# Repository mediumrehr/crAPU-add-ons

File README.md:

# crAPU-add-ons
a crappy Audio Processing Unit SAO for DEF CON 26 badges; specifically, the zinthesizer was designed for the [DCZia DC26 badge](https://github.com/dczia/Defcon26-Badge) and the scaremin was designed for [Chris Gammell's](https://twitter.com/Chris_Gammell) Goodfear badge.

[video demo](https://www.youtube.com/watch?v=xHMZxM6m_c0)

crAPUs were designed to add audio sythesis/playback capabilities to badges that didn't have any. Since i2c would not be fast enough to drive an external digital to analog converter (DAC), the crAPUs feature their own processor (SAM21G18) to generate tones, and the note and volume can be selected over i2c.

## Installing/Updating Firmware

### Setup

Firmware can be loaded with [Atmel Studio 7.0](https://www.microchip.com/mplab/avr-support/atmel-studio-7), or install the packages below to use with your preferred text editor and compile with arm gcc.

#### arm gcc and gdb

MacOS

```
brew install armmbed/formulae/arm-none-eabi-gcc
```

#### jlink gdb server

Download install file from [segger.com](https://www.segger.com/products/debug-probes/j-link/tools/j-link-gdb-server/about-j-link-gdb-server/)

#### SWD connection

Software debug (SWD) pins are labelled on the back-right of the boards. Connect SWDIO, SWCLK, 3V3, RESET, and GND as labelled. SWD requires the board to be powered external from the SWD port, so it's easiest to power the board from the 3V3 and GND pins on the SAO header.

### Build

```
cd firmware/crAPU/
make -C Build/
```

### Load

#### jlink

Start jlink gdb server in one tab

```
JLinkGDBServer -if SWD -device ATSAMD21G18
```

Start gdb in another tba

```
arm-none-eabi-gdb Build/crAPU.elf
(gdb) target extended-remote :2331
```

Load new firmware, reset microcontroller, and run new code

```
(gdb) load
(gdb) monitor reset
(gdb) c
```

## Usage

The crAPU can be controlled via i2c at address `0x1A`. The add-on will listen for two bytes, the first byte will set the note (0 - 127 using MIDI table), and the second byte will set the volume (0 - 127). If `128 (0x80)` is sent as the MIDI note, it will be interpreted as a note off command.

#### DCZia Badge

Load my [DCZia fork](https://github.com/mediumrehr/Defcon26-Badge) onto the DCZia badge. Attach the zinthesizer add-on, turn on the badge, and within menu mode, select button 7 (left column, third down). The display should now say it's in zinthesizer mode and each key will play a unique note.

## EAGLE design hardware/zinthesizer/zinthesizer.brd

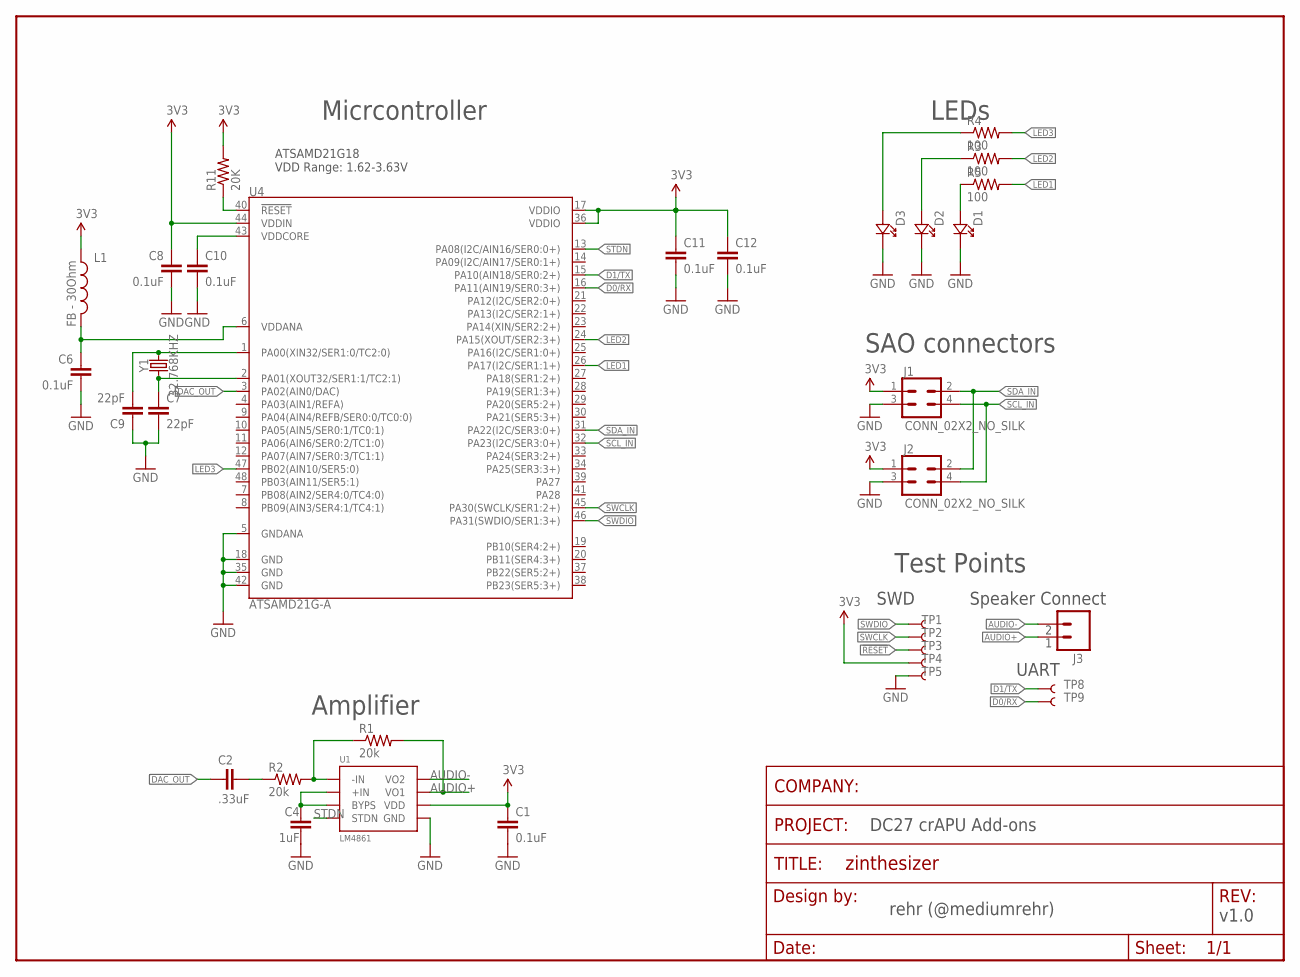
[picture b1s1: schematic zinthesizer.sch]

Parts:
C1, C6, C8, C10, C11, C12: 0.1uF; 0603-CAP
C2: .33uF; 0603-CAP
C4: 1uF; 0603-CAP
C7, C9: 22pF; 0603-CAP
D1, D2, D3: LED1206REVERSE_NO_SILK; 1206_NO_SILK
FRAME1: FRAME-LETTER-BLANKNO_PACKAGE; DUMMY
J1, J2: CONN_02X2_NO_SILK; 2X2_NO_SILK
J3: M02ROUND; M02_ROUND
L1: FB - 30Ohm; 0603
R1, R2: 20k; 0805
R3, R4, R5: 100; 0603-RES
R11: 20K; 0603-RES
TP1, TP2, TP3, TP4, TP5: TEST-POINT3X5; PAD.03X.05
TP8, TP9: TEST-POINT3X4; PAD.03X.04
U1: LM4861; 8-SOIC
U4: ATSAMD21G-A; TQFP-48
Y1: 32.768KHZ; ABS06

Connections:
3.3V: C1.1, C8.1, C11.1, C12.1, J1.1, J2.1, L1.1, R11.2, TP4.P$1, U1.P$6 (VDD), U4.17 (VDDIO), U4.36 (VDDIO), U4.44 (VDDIN)
!RESET: R11.1, TP3.P$1, U4.40 (!RESET!)
AUDIO+: J3.P$1, R1.2, U1.P$5 (VO1)
AUDIO-: J3.P$2, U1.P$8 (VO2)
D0/RX: TP9.P$1, U4.16 (PA11(AIN19/SER0:3+))
D1/TX: TP8.P$1, U4.15 (PA10(AIN18/SER0:2+))
DAC_OUT: C2.2, U4.3 (PA02(AIN0/DAC))
GND: C1.2, C4.2, C6.2, C7.2, C8.2, C9.1, C10.2, C11.2, C12.2, D1.P$1, D2.P$1, D3.P$1, J1.3, J2.3, TP5.P$1, U1.P$7 (GND), U4.5 (GNDANA), U4.18 (GND), U4.35 (GND), U4.42 (GND)
LED1: R5.2, U4.26 (PA17(I2C/SER1:1+))
LED2: R3.2, U4.24 (PA15(XOUT/SER2:3+))
LED3: R4.2, U4.47 (PB02(AIN10/SER5:0))
unnamed: C2.1, R2.1
unnamed: R1.1, R2.2, U1.P$4 (-IN)
unnamed: D1.P$2, R5.1
unnamed: C7.1, U4.2 (PA01(XOUT32/SER1:1/TC2:1)), Y1.P$1 (1)
unnamed: C4.1, U1.P$2 (BYPS), U1.P$3 (+IN)
unnamed: D2.P$2, R3.1
unnamed: D3.P$2, R4.1
unnamed: C9.2, U4.1 (PA00(XIN32/SER1:0/TC2:0)), Y1.P$2 (2)
SCL_IN: J1.4, J2.4, U4.32 (PA23(I2C/SER3:0+))
SDA_IN: J1.2, J2.2, U4.31 (PA22(I2C/SER3:0+))
STDN: U1.P$1 (STDN), U4.13 (PA08(I2C/AIN16/SER0:0+))
SWCLK: TP2.P$1, U4.45 (PA30(SWCLK/SER1:2+))
SWDIO: TP1.P$1, U4.46 (PA31(SWDIO/SER1:3+))
VDDANA: C6.1, L1.2, U4.6 (VDDANA)
VDDCORE: C10.1, U4.43 (VDDCORE)

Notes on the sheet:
ATSAMD21G18 VDD Range: 1.62-3.63V
DC27 crAPU Add-ons
rehr (@mediumrehr)
v1.0
Micrcontroller
LEDs
SAO connectors
Test Points
Amplifier
SWD
Speaker Connect
UART

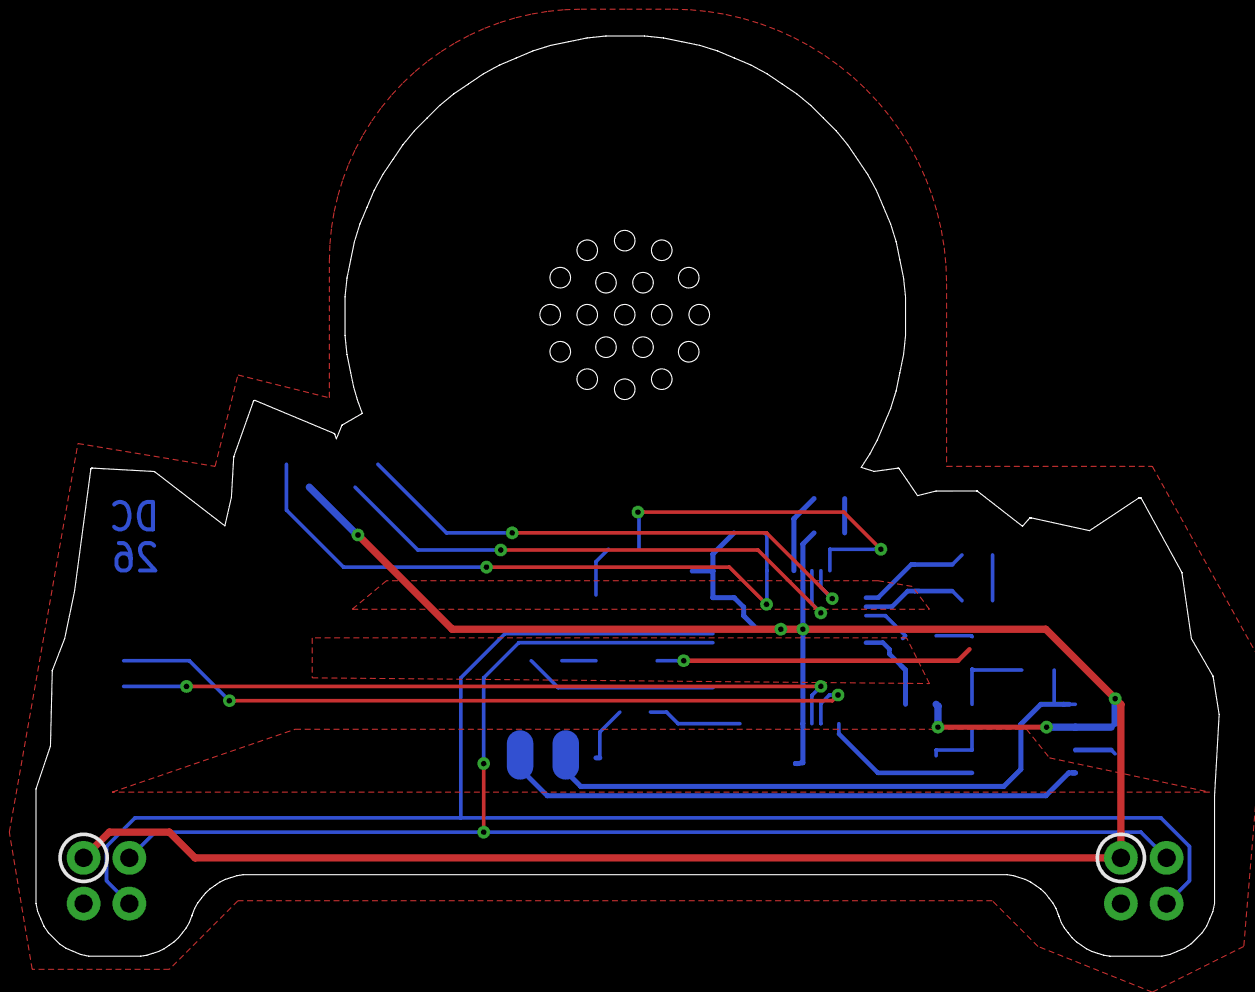
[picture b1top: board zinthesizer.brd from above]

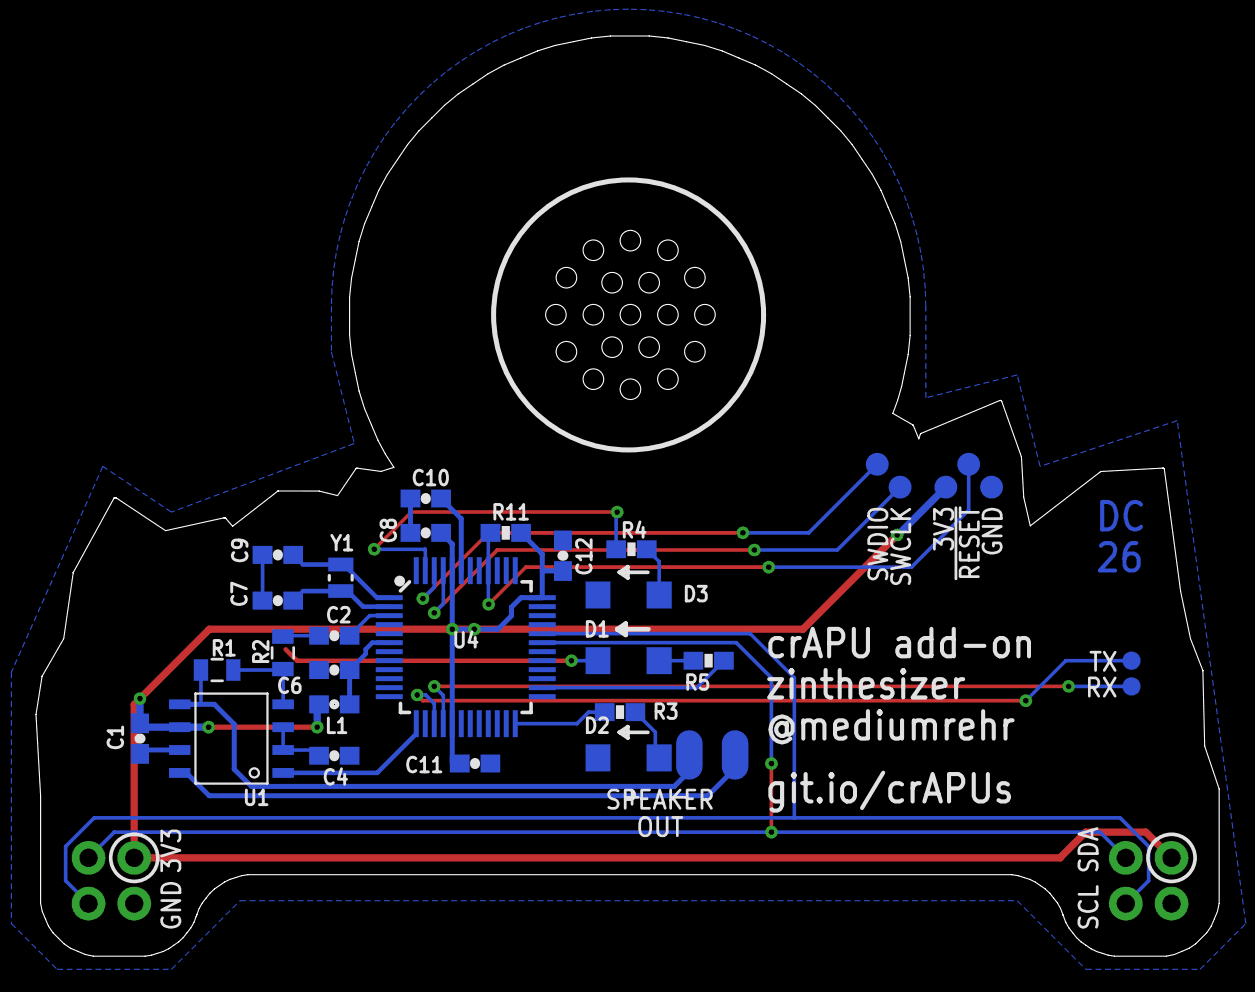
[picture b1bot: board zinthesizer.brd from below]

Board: 2 copper layers, 65.7 x 51.1 mm, 34 parts (31 on the bottom side), 26 nets.

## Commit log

2019-04-19 fix readme typo
2019-04-26 enable DAC (only 440Hz output)
2019-04-27 add i2c AND basic pitch control over i2c
2019-04-28 add hardware design files and BOM
2019-04-28 enable volume control and improve waveform resolution
2019-04-28 add link to DCZia forked repo
2019-05-25 add link to video demo
2019-05-28 fix i2c address
2019-05-28 add usage documentation

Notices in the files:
parts and their libraries:
SparkFun-Passives: Licensing: Creative Commons ShareAlike 4.0 International - https://creativecommons.org/licenses/by-sa/4.0
SparkFun-Aesthetics: Released under the Creative Commons Attribution Share-Alike 4.0 License
SparkFun-Aesthetics: https://creativecommons.org/licenses/by-sa/4.0
